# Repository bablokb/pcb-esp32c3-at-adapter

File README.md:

Adapter-PCB for ESP32C3 SuperMini Running ESP-AT Firmware
=========================================================

This small breakout for the ESP32C3 SuperMini adds an Stemma/Qt
connector for the pins of UART1. This allows the ESP32C3 to be used as
a wifi co-processor. The other side of the Stemma/Qt must be connected
to power, ground and an UART of the host MCU. This could also be a
Stemma/Qt connector, if the respective pins of the host can also be
repurposed from I2C to UART.

Note: the VCC of the Stemma/Qt is connected to 3V3. The SuperMini is
usually happy with this direct 3V3 power-supply (this skips the
internal regulator).  As an alternative, change the jumper on the back
to 5V and feed 3.3-6V from the host MCU.  According to the datasheet
of the regulator, it does not deliver 3.3V with an input lower than
about 3.5V, but my tests show that the SuperMini is robust in this
respect.

The SuperMini can also be used in standalone mode. In this case, the Stemma/Qt
serves as an ordinary I2C connector.

See <https://github.com/bablokb/circuitpython-esp32at> for a software solution.

Ready to use production files for JLCPCB are in the directory `production_files/`.

Schematic
---------

Layout
------

3D-Views
--------

License
-------

[![CC BY-SA 4.0][cc-by-sa-shield]][cc-by-sa]

This work is licensed under a
[Creative Commons Attribution-ShareAlike 4.0 International
License][cc-by-sa].

[![CC BY-SA 4.0][cc-by-sa-image]][cc-by-sa]

[cc-by-sa]: http://creativecommons.org/licenses/by-sa/4.0/
[cc-by-sa-image]: https://licensebuttons.net/l/by-sa/4.0/88x31.png
[cc-by-sa-shield]:
https://img.shields.io/badge/License-CC%20BY--SA%204.0-lightgrey.svg

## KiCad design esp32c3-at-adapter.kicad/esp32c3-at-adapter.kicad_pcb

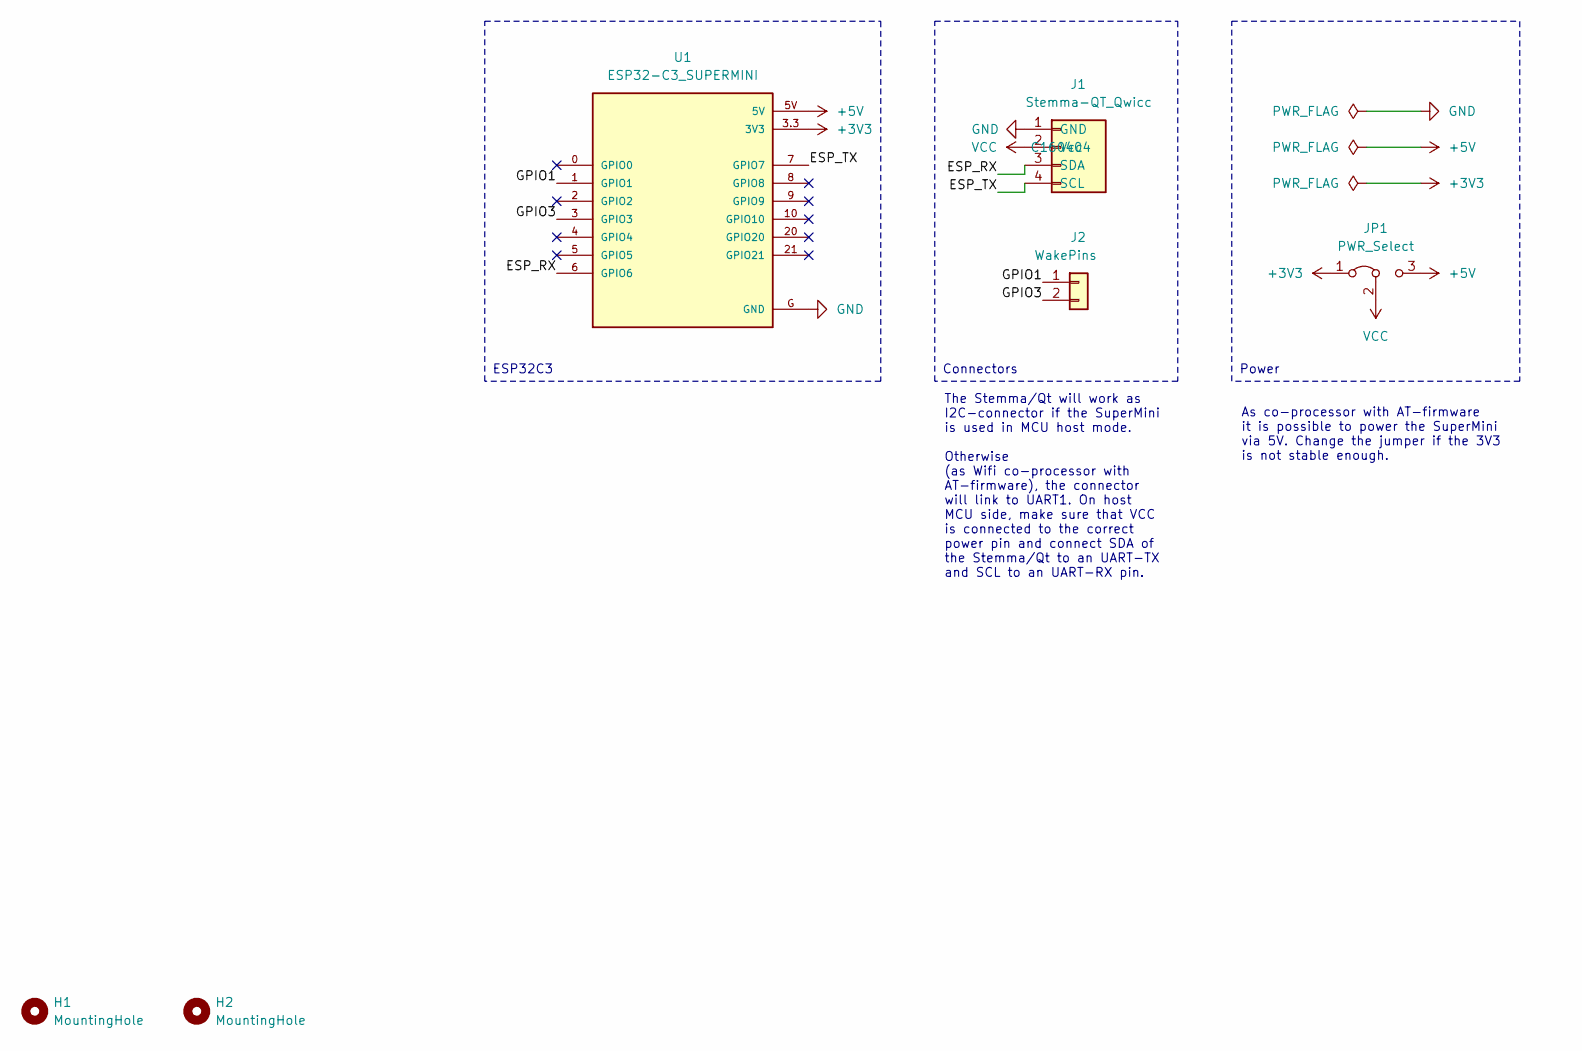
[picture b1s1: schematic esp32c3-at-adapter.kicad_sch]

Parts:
H1, H2: MountingHole; MountingHole_2.5mm
J1: Stemma-QT_Qwicc; JST_SH_SM04B-SRSS-TB_1x04-1MP_P1.00mm_Horizontal; LCSC C160404
J2: WakePins; PinHeader_1x02_P2.54mm_Vertical
JP1: PWR_Select; SolderJumper-3_P1.3mm_Bridged12_Pad1.0x1.5mm
U1: ESP32-C3_SUPERMINI

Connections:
+3V3: JP1.1 (A), U1.3.3 (3V3)
+5V: JP1.3 (B), U1.5V
/ESP_RX: J1.3 (SDA), U1.6 (GPIO6)
/ESP_TX: J1.4 (SCL), U1.7 (GPIO7)
/GPIO1: J2.1, U1.1 (GPIO1)
/GPIO3: J2.2, U1.3 (GPIO3)
GND: J1.1 (GND), U1.G (GND)
VCC: J1.2 (Vcc), JP1.2 (C)

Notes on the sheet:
Power
ESP32C3
Connectors
As co-processor with AT-firmware it is possible to power the SuperMini via 5V. Change the jumper if the 3V3 is not stable enough.
The Stemma/Qt will work as I2C-connector if the SuperMini is used in MCU host mode. Otherwise (as Wifi co-processor with AT-firmware), the connector will link to UART1. On host MCU side, make sure that VCC is connected to the correct power pin and connect SDA of the Stemma/Qt to an UART-TX and SCL 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

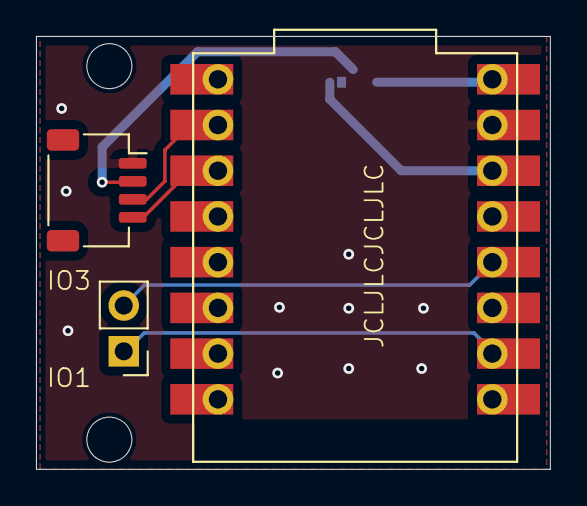
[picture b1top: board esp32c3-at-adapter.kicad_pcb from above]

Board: 2 copper layers, 28.5 x 24.1 mm, 6 parts (1 on the bottom side), 8 nets.

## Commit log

2024-09-26 initial version
2024-09-26 Rev: 0.90 (first production test)
